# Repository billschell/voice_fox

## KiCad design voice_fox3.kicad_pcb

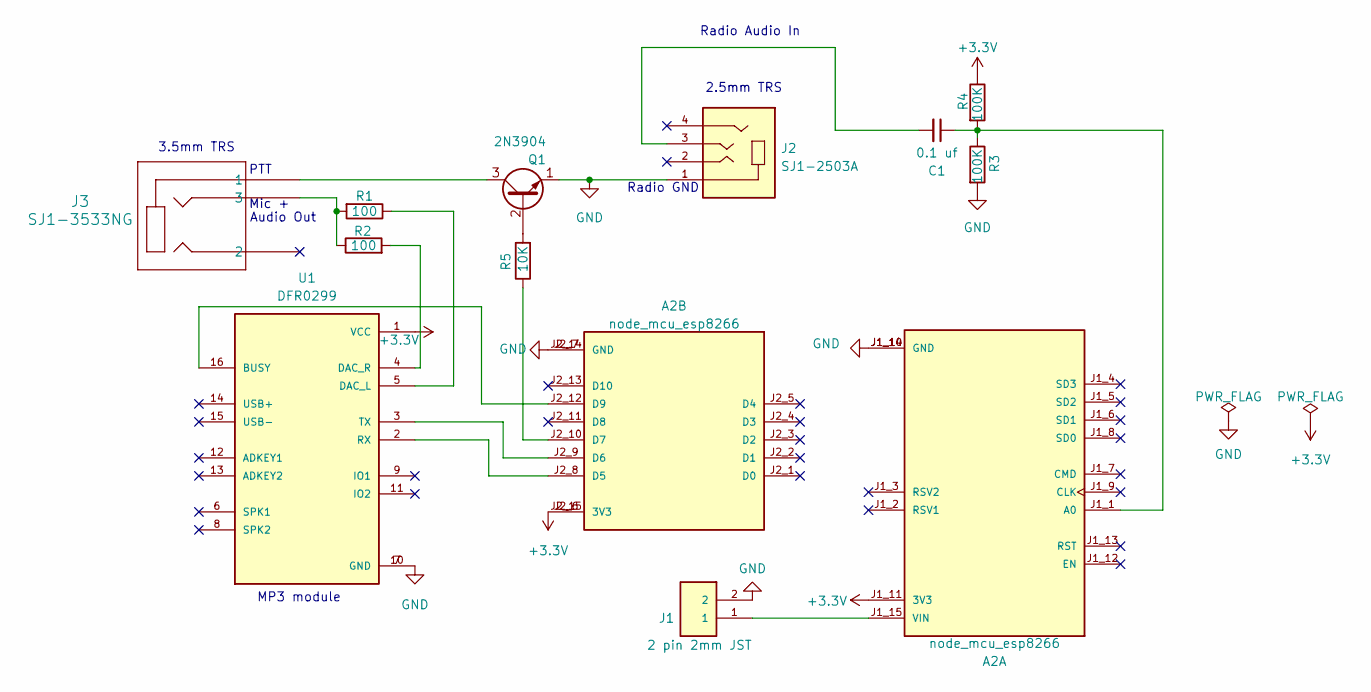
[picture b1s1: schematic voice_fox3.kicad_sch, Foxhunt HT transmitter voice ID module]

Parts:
A2: node_mcu_esp8266; PARTREV N/A
C1: 0.1 uf; C_Disc_D4.7mm_W2.5mm_P5.00mm
J1: 2 pin 2mm JST; JST_B2B-PH-K-S(LF)(SN); PARTREV N/A; DIGI-KEY_PART_NUMBER 455-1704-ND
J2: SJ1-2503A; CUI_SJ1-2503A
J3: SJ1-3533NG; SJ1-3533NG_CUD
Q1: 2N3904; TO-92_HandSolder
R1, R2: 100; R_Axial_DIN0207_L6.3mm_D2.5mm_P10.16mm_Horizontal
R3, R4: 100K; R_Axial_DIN0207_L6.3mm_D2.5mm_P10.16mm_Horizontal
R5: 10K; R_Axial_DIN0207_L6.3mm_D2.5mm_P10.16mm_Horizontal
U1: DFR0299; MODULE_DFR0299

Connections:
+3.3V: A2.J1_11 (3V3), A2.J2_6 (3V3), A2.J2_15 (3V3), R4.1, U1.1 (VCC)
GND: A2.J1_10 (GND), A2.J1_14 (GND), A2.J2_7 (GND), A2.J2_14 (GND), J1.2, J2.1, Q1.1 (E), R3.2, U1.7 (GND), U1.10 (GND)
unnamed: A2.J1_1 (A0), C1.1, R3.1, R4.2
unnamed: A2.J1_15 (VIN), J1.1
unnamed: A2.J2_8 (D5), U1.2 (RX)
unnamed: A2.J2_9 (D6), U1.3 (TX)
unnamed: A2.J2_10 (D7), R5.1
unnamed: A2.J2_12 (D9), U1.16 (BUSY)
unnamed: C1.2, J2.3
unnamed: J3.3, R1.2, R2.1
unnamed: Q1.2 (B), R5.2
unnamed: J3.1, Q1.3 (C)
unnamed: R1.1, U1.5 (DAC_L)
unnamed: R2.2, U1.4 (DAC_R)

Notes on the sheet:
Radio GND
PTT
2.5mm TRS
Mic +
Radio Audio In
3.5mm TRS
MP3 module
Audio Out

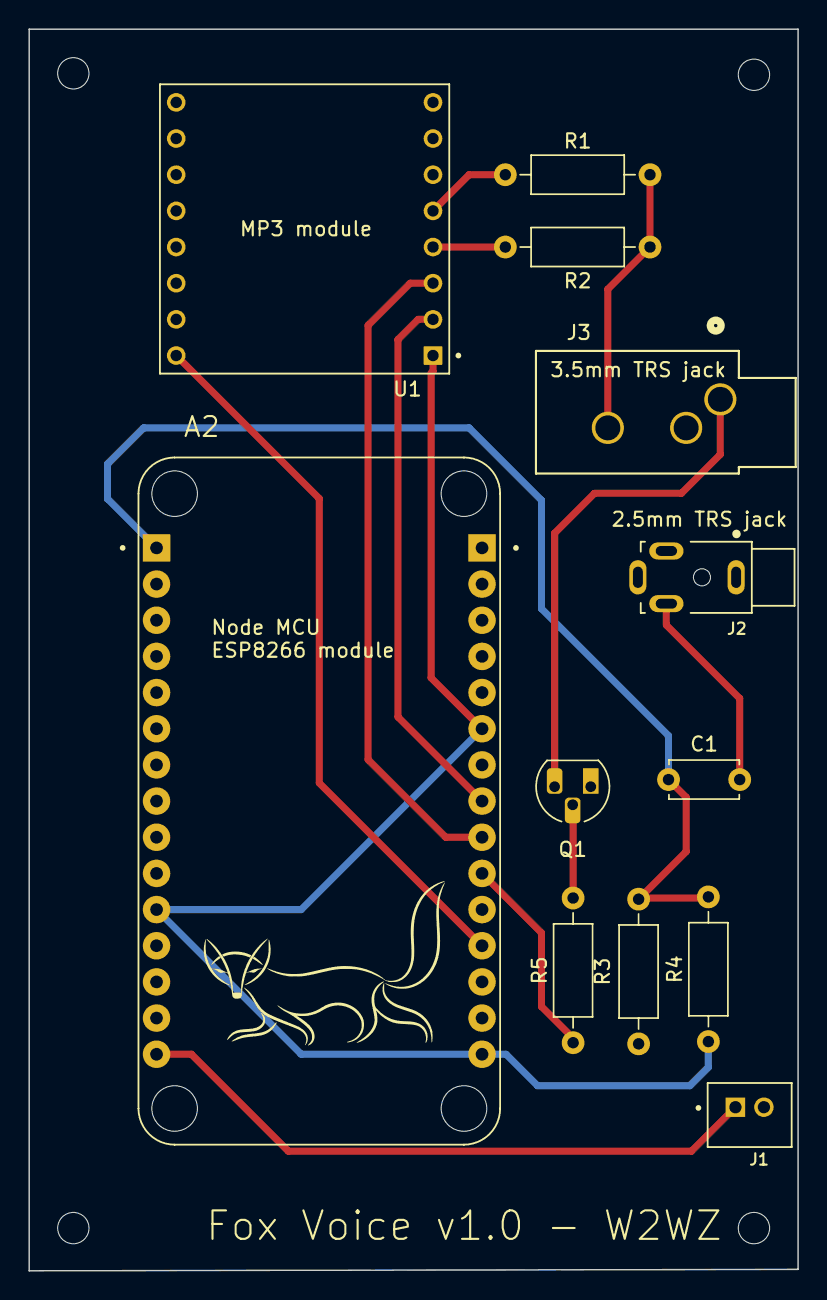
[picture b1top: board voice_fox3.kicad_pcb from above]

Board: 2 copper layers, 54.0 x 87.2 mm, 16 parts (0 on the bottom side), 14 nets.

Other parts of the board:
H0, H1, H2, H3: MountingHole_2.2mm_M2

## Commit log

2023-05-16 add gitignore
2023-05-26 revised to use a BJT for PTT switching
2023-05-26 added audio in to mcu ADC
2023-05-26 added audio in to mcu ADC, added 3v3 net
2023-05-26 updated pcb from schematic
2023-05-26 initial placement
2023-06-19 many changes
